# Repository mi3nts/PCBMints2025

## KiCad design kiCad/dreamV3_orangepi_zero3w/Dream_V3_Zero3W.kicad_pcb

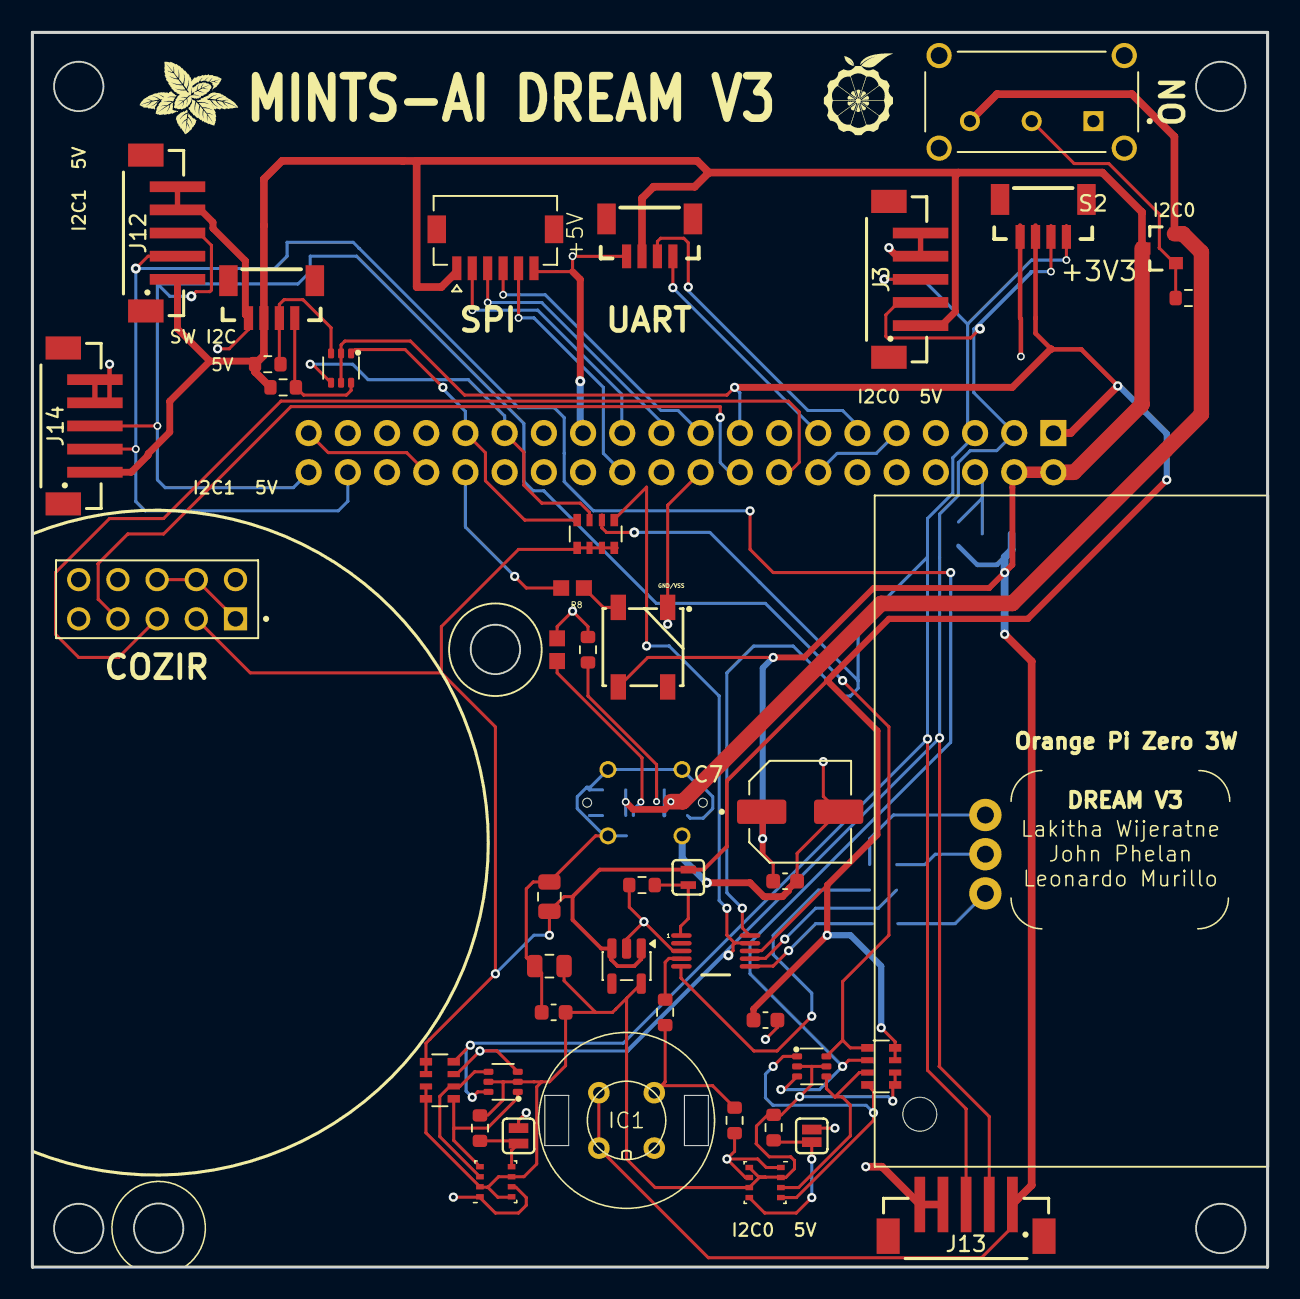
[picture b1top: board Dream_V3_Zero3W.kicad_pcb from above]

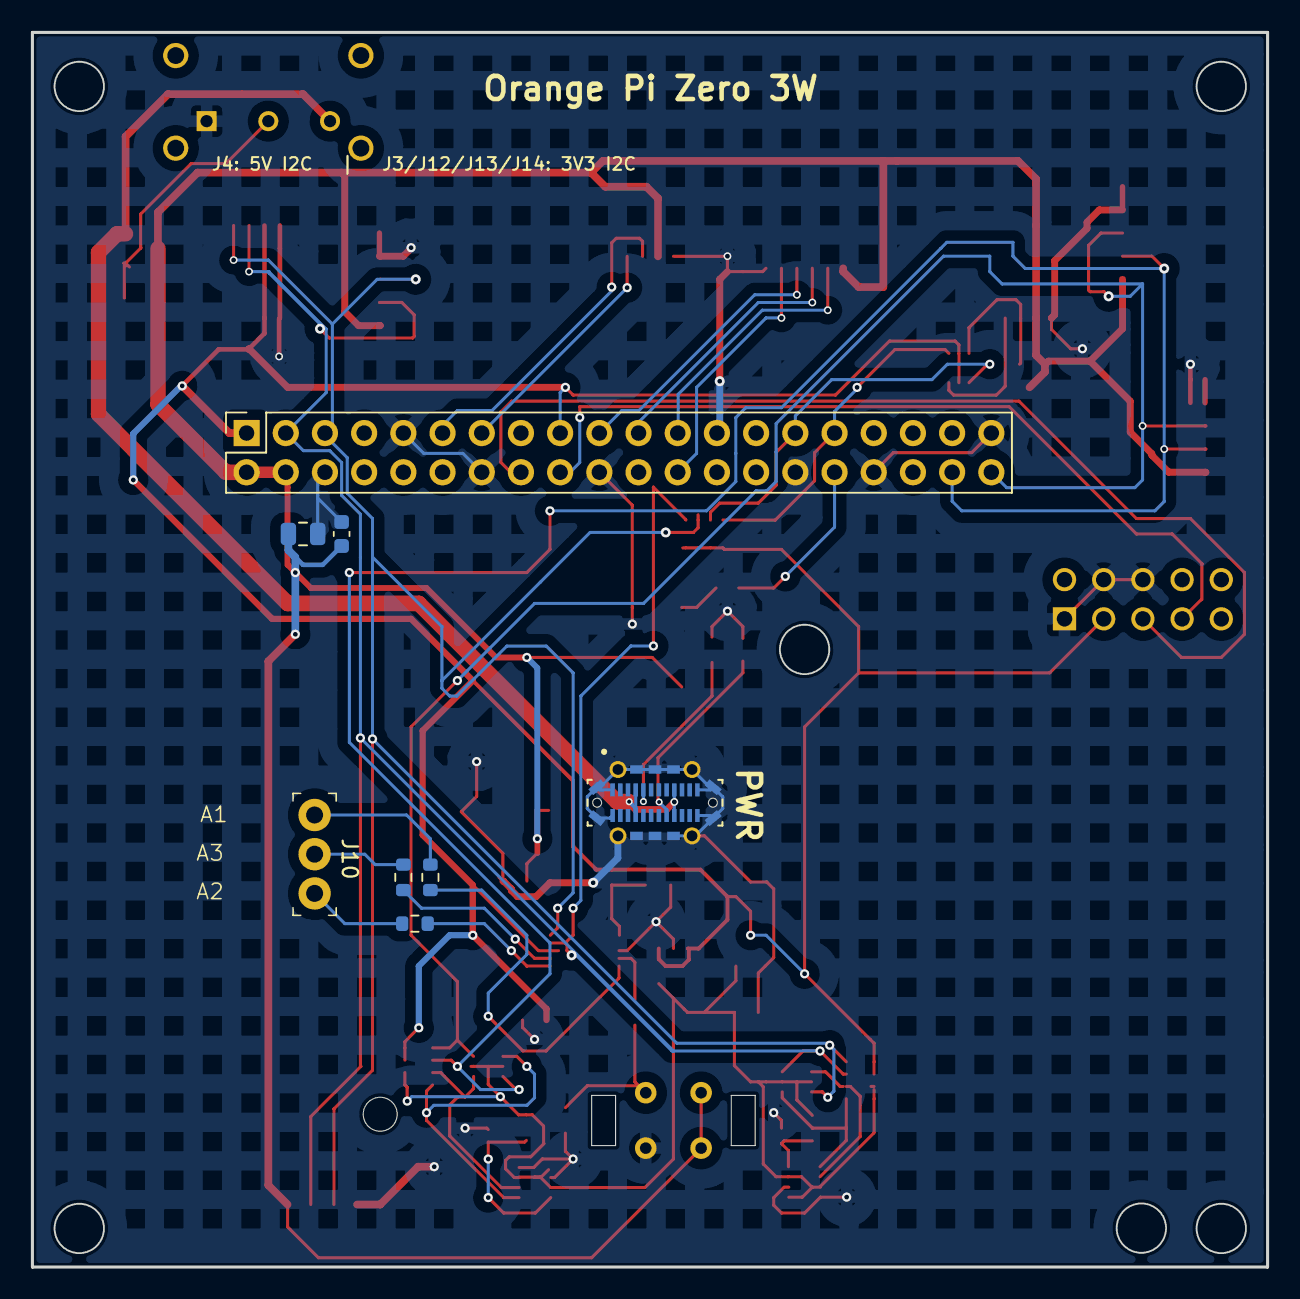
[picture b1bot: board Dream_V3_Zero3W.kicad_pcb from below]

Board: 2 copper layers, 80.0 x 80.0 mm, 51 parts (8 on the bottom side), 41 nets.

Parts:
C1, C5, C6, C8: 0.1uF; C_0603_1608Metric
C2, C3, C4: 10uF; C_0805_2012Metric
C7: EEV107M010S9GAA
D1: WS2812B_5050; WS2812_5050-4Pin
IC1: TGS2611-C00; tgs2611c00
J1: GPIO; PinSocket_2x20_P2.54mm_Vertical
J3, J12, J13, J14: 679305124022
J4, J6: Qwiic_Vertical; JST_1x04_P1.0mm_Vertical_SMD
J5: M20-7830542
J7: 5013310607; MOLEX_5013310607
J8: Qwiic_4pin_Vertical; JST_1x04_P1.0mm_Vertical_SMD
J10: 640456-3; PinHeader_1x3_P2.54_Drill1.1mm
J11: 10132328-10011LF; AMPHENOL_10132328-10011LF
JP1, JP2, JP4: Jumper_2_NO
Q1, Q2, Q4: BSS138; SOT-363
Q3: MOT2301B2; SOT23-3
R1, R5, R13: 10k; R_Array_Convex_4x0603
R2: 100k; R_0603_1608Metric
R3: 1k; R_0603_1608Metric
R6: RC0603FR-075K1L; RESC1607X60N
R7: 5.1k; R_0603_1608Metric
R8: RC0603FR-07330RL; RESC1607X60N
R9, R10, R14, R15, R17, R19, R20, R21, R22: 10k; R_0603_1608Metric
S2: EG1224; SW_EG1224
U1: AP2112K-3.3; SOT-23-5
U2, U5: BME280; Bosch_LGA-8_2.5x2.5mm_P0.65mm_ClockwisePinNumbering
U3: ADS1115IDGST; DGS0010A_New

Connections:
+3V3: C2.1, C8.2, J1.1, J1.17, J5.3, J8.2, JP2.2 (B), Q4.2 (G), Q4.5 (G), R1.1, R1.2, R5.2, R5.4, R5.6, R5.8, R13.7, R13.8, U1.1 (VIN), U1.en, U3.8 (VDD)
+5V: C4.1, C5.1, C6.1, C7.P, D1.1 (VDD), IC1.3 (SENSOR_ELECTRODE_(+)), IC1.4 (HEATER_2), J1.2, J1.4, J3.1, J4.2, J6.2, J7.1, J12.1, J13.1, J14.1, Q3.3 (D_3), R14.1, R15.2
/5V_BUS_USB: J11.A4 (VBUS_A4), J11.A9 (VBUS_A9), J11.B4 (VBUS_B4), J11.B9 (VBUS_B9), Q3.5, R2.2, S2.3
/ADS_ADDR: JP2.1 (A), R17.2, U3.1 (ADDR)
/ADS_ANALOG_0: IC1.2 (SENSOR_ELECTRODE_(-)), R3.2, R19.2
/ADS_ANALOG_1: J10.1, R20.2
/ADS_ANALOG_2: J10.3, R21.2
/ADS_ANALOG_3: J10.2, R22.2
/BME_ADD_1: JP1.2 (B), R9.1, U5.5 (SDO)
/BME_ADD_2: JP4.2 (B), R10.1, U2.5 (SDO)
/BME_SCL1: Q1.1 (S), R1.5, U5.4 (SCK)
/BME_SCL2: Q2.1 (S), R13.4, U2.4 (SCK)
/BME_SDA1: Q1.4 (S), R1.6, U5.3 (SDI)
/BME_SDA2: Q2.4 (S), R13.3, U2.3 (SDI)
/BUS3_SCL_SHIFT: J4.4, Q4.6 (D), R15.1
/BUS3_SDA_SHIFT: J4.3, Q4.3 (D), R14.2
/PB0/UART2_TX: J1.11, J6.3
/PB1/UART2_RX: J1.13, J6.4
/PB2/I2C0_SCL: J1.5, J3.3, J8.4, J13.3, Q1.6 (D), R1.8, R5.3, U3.10 (SCL)
/PB3/I2C0_SDA: J1.3, J3.2, J8.3, J13.2, Q1.3 (D), R1.7, R5.1, U3.9 (SDA)
/PB7/I2C1_SCL: J1.40, J12.3, J14.3, Q2.6 (D), R13.1
/PB8/I2C1_SDA: J1.38, J12.2, J14.2, Q2.3 (D), R13.2
/PD1/PWM0_1: J1.32, R8.2
/PE0/SPI3_CS0: J1.24, J7.5
/PE1/SPI3_CLK: J1.23, J7.2
/PE2/SPI3_MOSI: J1.19, J7.4
/PE3/SPI3_MISO: J1.21, J7.3
/PE12/SW_SDA: J1.29, Q4.4 (S), R5.5
/PE13/SW_SCL: J1.31, Q4.1 (S), R5.7
/PL2/UART7_TX: J1.16, J5.5
/PL3/UART7_RX: J1.18, J5.7
/SWITCH_GATE: Q3.1, R2.1, S2.2
BME_3V3: C1.1, C3.1, Q1.2 (G), Q1.5 (G), Q2.2 (G), Q2.5 (G), R1.3, R1.4, R9.2, R10.2, R13.5, R13.6, U1.5 (VOUT), U2.2 (CSB), U2.6 (VDDIO), U2.8 (VDD), U5.2 (CSB), U5.6 (VDDIO), U5.8 (VDD)
GND: C1.2, C2.2, C3.2, C4.2, C5.2, C6.2, C7.N, C8.1, D1.3 (VSS), IC1.1 (HEATER_1), J1.6, J1.9, J1.14, J1.20, J1.25, J1.30, J1.34, J1.39, J3.4, J3.5, J4.1, J5.1, J5.4, J5.6, J6.1, J7.6, J8.1, J11.1 (SHIELD), J11.2 (SHIELD__1), J11.3 (SHIELD__2), J11.4 (SHIELD__3), J11.5 (SHIELD__4), J11.6 (SHIELD__5), J11.7 (SHIELD__6), J11.8 (SHIELD__7), J11.9 (SHIELD__8), J11.10 (SHIELD__9), J11.11 (SHIELD__10), J11.12 (SHIELD__11), J11.13 (SHIELD__12), J11.14 (SHIELD__13), J11.A1 (GND_A1), J11.A12 (GND_A12), J11.B1 (GND_B1), J11.B12 (GND_B12), J12.4, J12.5, J13.4, J13.5, J14.4, J14.5, JP1.1 (A), JP4.1 (A), R3.1, R6.1, R7.1, R17.1, S2.1, U1.2 (GND), U2.1 (GND), U2.7 (GND), U3.3 (GND), U5.1 (GND), U5.7 (GND)
unnamed: D1.4 (DIN), R8.1
unnamed: J11.A5 (CC1), R7.2
unnamed: J11.B5 (CC2), R6.2
unnamed: R19.1, U3.4 (AIN0)
unnamed: R20.1, U3.5 (AIN1)
unnamed: R21.1, U3.6 (AIN2)
unnamed: R22.1, U3.7 (AIN3)

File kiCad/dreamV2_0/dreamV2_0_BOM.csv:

"Id";"Designator";"Footprint";"Quantity";"Designation";"Supplier and ref";
1;"J3";"679305124022";1;"679305124022";;;
2;"JP3,JP1,JP2";"Jumper_2_NO";3;"~";;;
3;"U1";"SOT-23-5";1;"AP2112K-3.3";;;
4;"U2";"Bosch_LGA-8_2.5x2.5mm_P0.65mm_ClockwisePinNumbering";1;"BME280";;;
5;"C6,C5,C1";"C_0603_1608Metric";3;"0.1uF";;;
6;"J4,J2,J9,J6,J8";"JST_SMD_1.0mm-4_Vertical_Black";5;"Qwiic_Vertical";;;
7;"R2,R3";"R_0603_1608Metric";2;"10k";;;
8;"J7";"5013310607";1;"5013310607";;;
9;"C4,C2,C3";"C_0805_2012Metric";3;"10uF";;;
10;"Q1";"SOT-363";1;"BSS138";;;
11;"U3";"SOT-23-8";1;"INA219BxDCN";;;
12;"R5,R1";"R_Array_Convex_4x0603";2;"10k";;;
13;"J5";"M20-7830542";1;"M20-7830542";;;
14;"S1";"SWITCH_NK236_APM";1;"NKK236";;;
15;"D1";"WS2812_5050-4Pin";1;"WS2812B_5050";;;
16;"R8";"RC0603FR-07330RL";1;"RC0603FR-07330RL";;;
17;"R4";"PT2512FK-070R1L";1;"PT2512FK-070R1L";;;
18;"C7";"EEV107M010S9GAA";1;"EEV107M010S9GAA";;;
19;"J1";"PinSocket_2x20_P2.54mm_Vertical";1;"GPIO";;;
20;"R7";"R_0603_1608Metric";1;"RC0603FR-075K1L";;;
21;"IC1";"TGS2611-C00_FGS";1;"TGS2611-C00";;;
22;"R6";"RC0603N_YAG-L";1;"RC0603FR-075K1L";;;
23;"J11";"10132328-10011LF";1;"10132328-10011LF";;;
